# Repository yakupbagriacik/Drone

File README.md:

# Open Source Arduino Drone Project
-This project has been developed as a prototaype for educational purposes, using an Arduino development board.

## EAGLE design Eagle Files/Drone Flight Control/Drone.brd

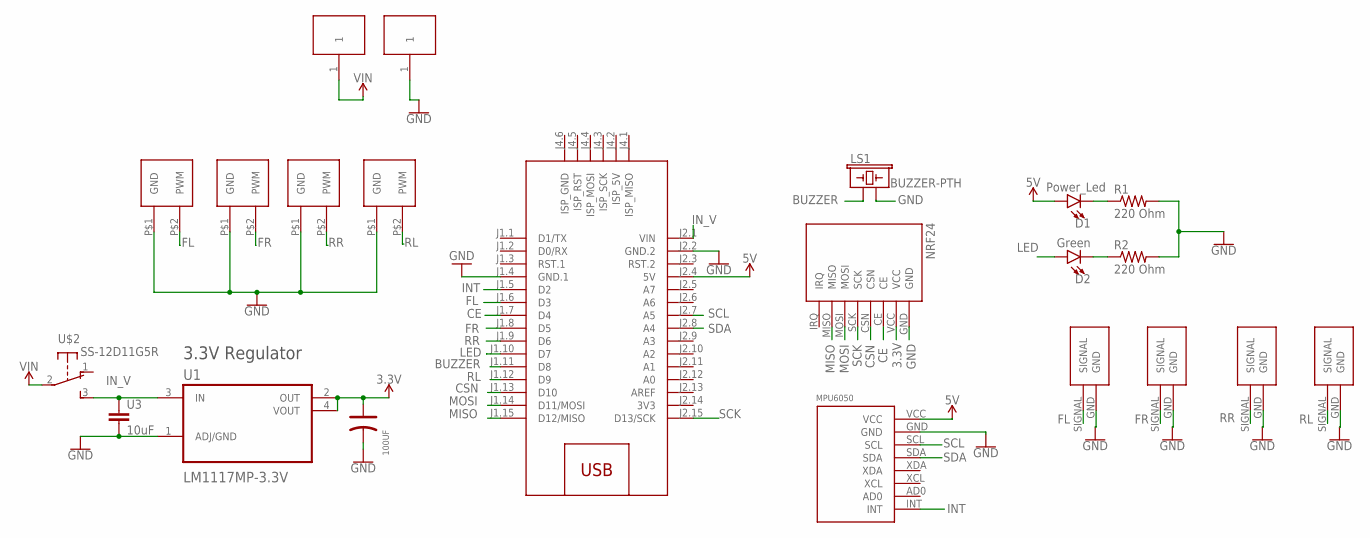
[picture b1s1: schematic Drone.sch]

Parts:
D1: Power_Led; LED_5MM
D2: Green; LED_5MM
LS1: BUZZER-PTH; BUZZER-12MM
M1: ARDUINO-NANO-3.0#ISP
R1, R2: 220 Ohm; RES_1206
U1: LM1117MP-3.3V; SOT230P700X180-4N
U2: 100UF; 8X10MM
U3: 10uF; 1206
U$1: MPU6050
U$2: SS-12D11G5R; SWITCH
U$3, U$4, U$6, U$7: PWM
U$5: NRF24
U$8, U$9: PAD
U$10, U$11, U$12, U$13: SIGNAL

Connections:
3.3V: U1.2 (OUT), U1.4 (VOUT), U2.1 (+), U$5.VCC
3V3: M1.J2.14 (3V3)
5V: D1.A, M1.J2.4 (5V), U$1.VCC
BUZZER: LS1.+ (1), M1.J1.11 (D8)
CE: M1.J1.7 (D4), U$5.CE
CSN: M1.J1.13 (D10), U$5.CSN
FL: M1.J1.6 (D3), U$3.P$2 (PWM), U$10.SIGNAL
FR: M1.J1.8 (D5), U$4.P$2 (PWM), U$11.SIGNAL
GND: LS1.- (2), M1.J1.4 (GND.1), M1.J2.2 (GND.2), R1.2, R2.2, U1.1 (ADJ/GND), U2.2 (-), U3.2, U$1.GND, U$3.P$1 (GND), U$4.P$1 (GND), U$5.GND, U$6.P$1 (GND), U$7.P$1 (GND), U$9.1, U$10.GND, U$11.GND, U$12.GND, U$13.GND
INT: M1.J1.5 (D2), U$1.INT
IN_V: M1.J2.1 (VIN), U1.3 (IN), U3.1, U$2.3 (S)
LED: D2.A, M1.J1.10 (D7)
MISO: M1.J1.15 (D12/MISO), U$5.MISO
MOSI: M1.J1.14 (D11/MOSI), U$5.MOSI
unnamed: D1.K (C), R1.1
unnamed: D2.K (C), R2.1
RL: M1.J1.12 (D9), U$7.P$2 (PWM), U$13.SIGNAL
RR: M1.J1.9 (D6), U$6.P$2 (PWM), U$12.SIGNAL
SCK: M1.J2.15 (D13/SCK), U$5.SCK
SCL: M1.J2.7 (A5), U$1.SCL
SDA: M1.J2.8 (A4), U$1.SDA
VIN: U$2.2, U$8.1

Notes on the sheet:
3.3V Regulator

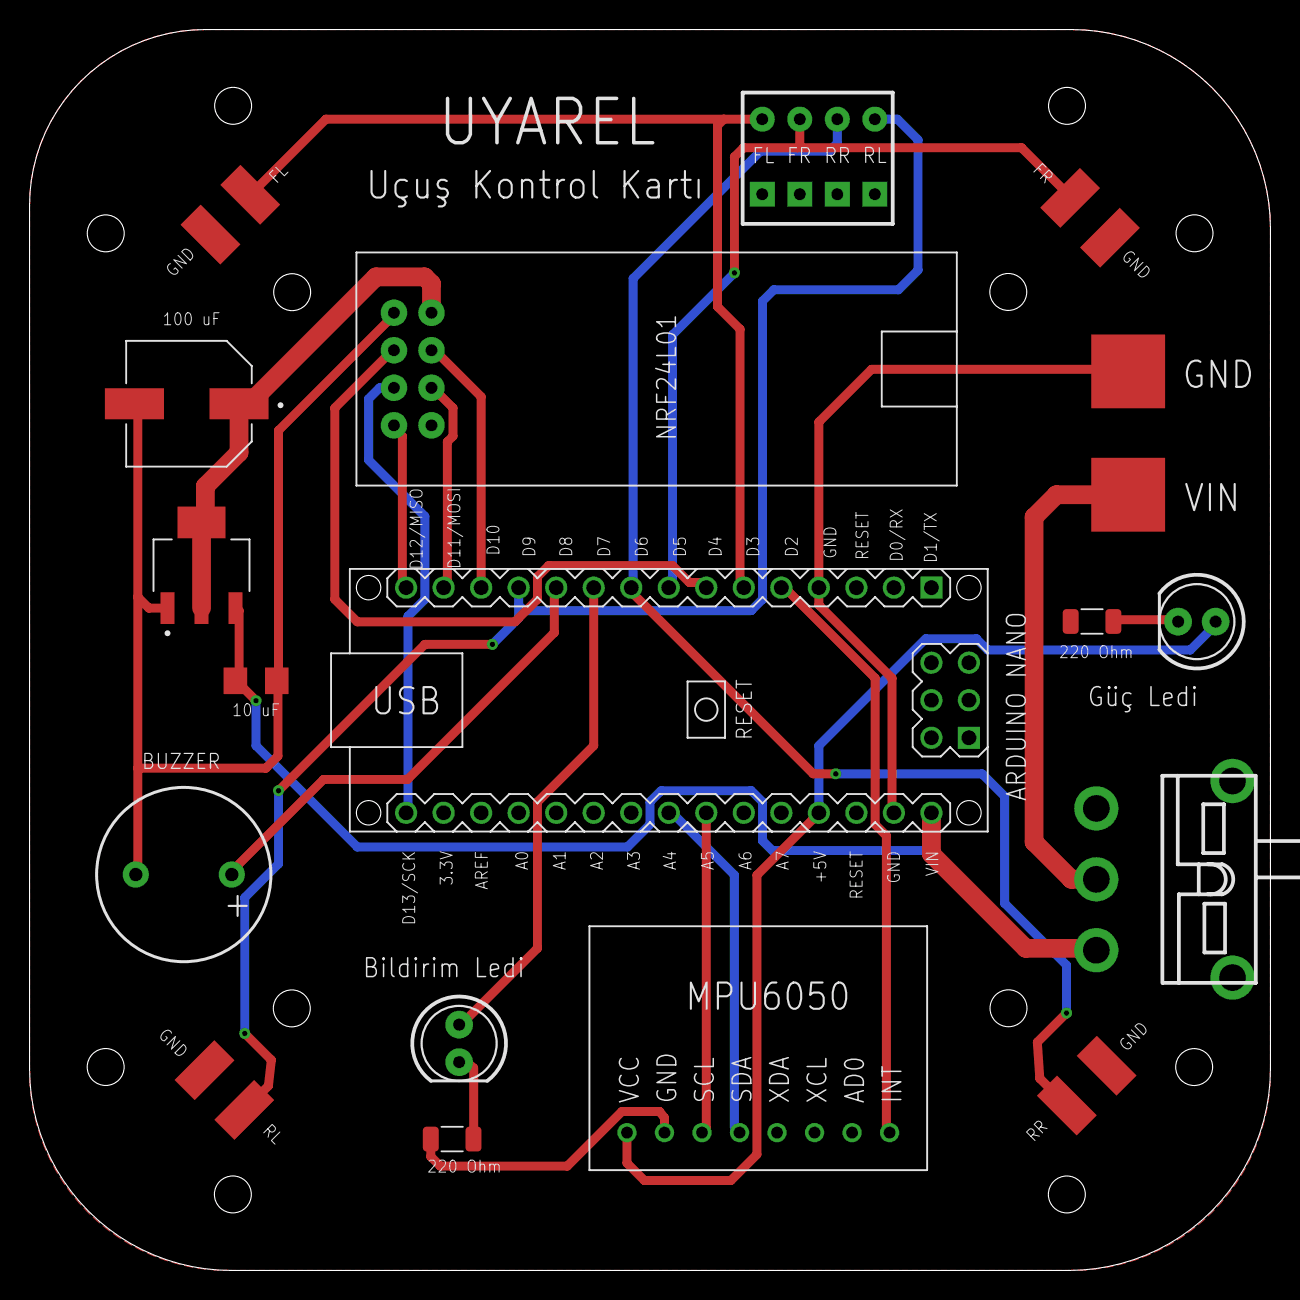
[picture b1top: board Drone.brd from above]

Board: 2 copper layers, 84.0 x 84.0 mm, 22 parts (0 on the bottom side), 21 nets.

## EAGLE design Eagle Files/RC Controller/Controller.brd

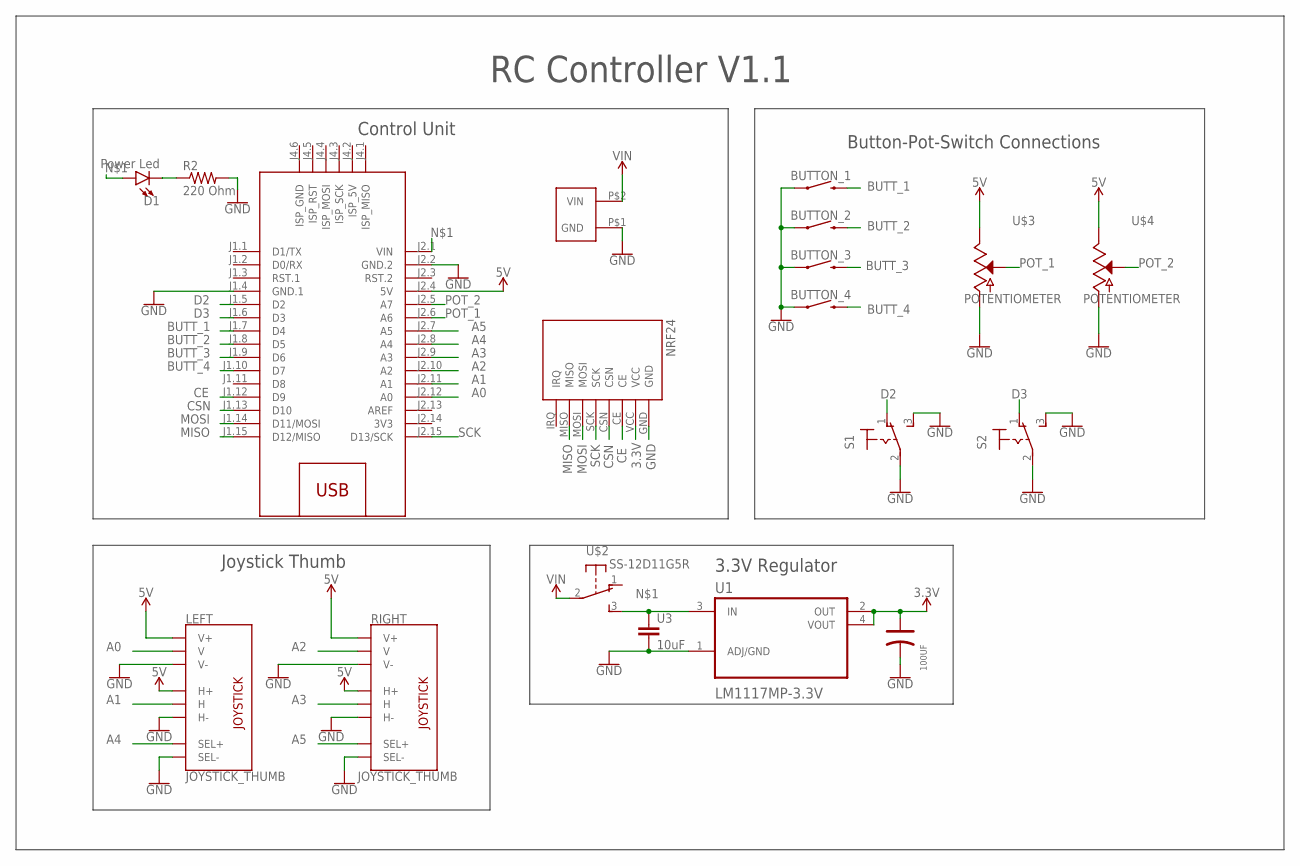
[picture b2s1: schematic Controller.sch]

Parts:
BUTTON_1, BUTTON_2, BUTTON_3, BUTTON_4: MOMENTARY-SWITCH-SPST-PTH-6.0MM; TACTILE_SWITCH_PTH_6.0MM
D1: Power Led; LED-1206
LEFT: JOYSTICK_THUMB; JOYSTICK
M1: ARDUINO-NANO-3.0#ISP
R2: 220 Ohm; RES_1206
RIGHT: JOYSTICK_THUMB; JOYSTICK
S1, S2: 320-916
U1: LM1117MP-3.3V; SOT230P700X180-4N
U2: 100UF; 8X10MM
U3: 10uF; 1206
U$1: VIN; SMD_VIN
U$2: SS-12D11G5R; SWITCH
U$3, U$4: POTENTIOMETER
U$5: NRF24

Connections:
3.3V: U1.2 (OUT), U1.4 (VOUT), U2.1 (+), U$5.VCC
3V3: M1.J2.14 (3V3)
5V: LEFT.H1 (H+), LEFT.V1 (V+), M1.J2.4 (5V), RIGHT.H1 (H+), RIGHT.V1 (V+), U$3.1, U$4.1
A0: LEFT.V2 (V), M1.J2.12 (A0)
A1: LEFT.H2 (H), M1.J2.11 (A1)
A2: M1.J2.10 (A2), RIGHT.V2 (V)
A3: M1.J2.9 (A3), RIGHT.H2 (H)
A4: LEFT.B1A (SEL+), M1.J2.8 (A4)
A5: M1.J2.7 (A5), RIGHT.B1A (SEL+)
BUTT_1: BUTTON_1.3 (2), M1.J1.7 (D4)
BUTT_2: BUTTON_2.3 (2), M1.J1.8 (D5)
BUTT_3: BUTTON_3.3 (2), M1.J1.9 (D6)
BUTT_4: BUTTON_4.3 (2), M1.J1.10 (D7)
CE: M1.J1.12 (D9), U$5.CE
CSN: M1.J1.13 (D10), U$5.CSN
D2: M1.J1.5 (D2), S1.1 (O)
D3: M1.J1.6 (D3), S2.1 (O)
GND: BUTTON_1.1, BUTTON_2.1, BUTTON_3.1, BUTTON_4.1, LEFT.B2A (SEL-), LEFT.H3 (H-), LEFT.V3 (V-), M1.J1.4 (GND.1), M1.J2.2 (GND.2), R2.2, RIGHT.B2A (SEL-), RIGHT.H3 (H-), RIGHT.V3 (V-), S1.2, S1.3 (S), S2.2, S2.3 (S), U1.1 (ADJ/GND), U2.2 (-), U3.2, U$1.P$1 (GND), U$3.3, U$4.3, U$5.GND
MISO: M1.J1.15 (D12/MISO), U$5.MISO
MOSI: M1.J1.14 (D11/MOSI), U$5.MOSI
unnamed: D1.A, M1.J2.1 (VIN), U1.3 (IN), U3.1, U$2.3 (S)
unnamed: D1.C, R2.1
POT_1: M1.J2.6 (A6), U$3.2
POT_2: M1.J2.5 (A7), U$4.2
SCK: M1.J2.15 (D13/SCK), U$5.SCK
VIN: U$1.P$2 (VIN), U$2.2

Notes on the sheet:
3.3V Regulator
Joystick Thumb
Button-Pot-Switch Connections
Control Unit
RC Controller V1.1

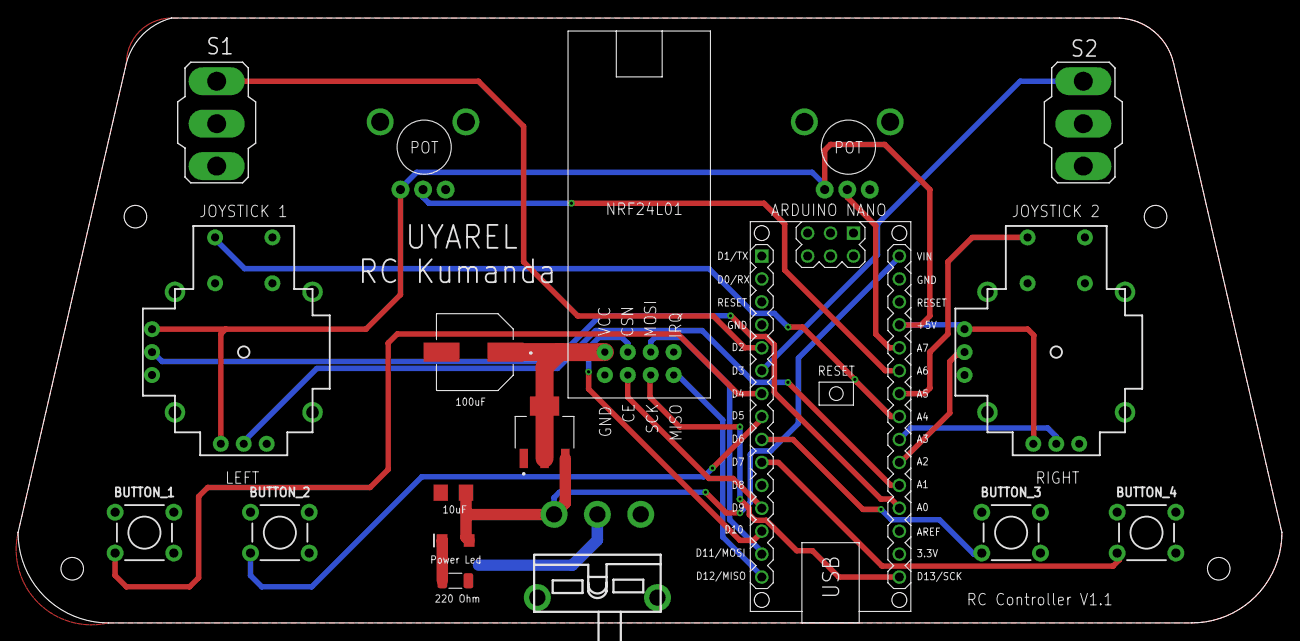
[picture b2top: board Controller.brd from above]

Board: 2 copper layers, 140.0 x 67.0 mm, 19 parts (1 on the bottom side), 25 nets.

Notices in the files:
parts and their libraries:
SparkFun-Capacitors: Licensing: Creative Commons ShareAlike 4.0 International - https://creativecommons.org/licenses/by-sa/4.0
diy-modules: Released under the Creative Commons Attribution 4.0 International License: http://creativecommons.org/licenses/by/4.0
